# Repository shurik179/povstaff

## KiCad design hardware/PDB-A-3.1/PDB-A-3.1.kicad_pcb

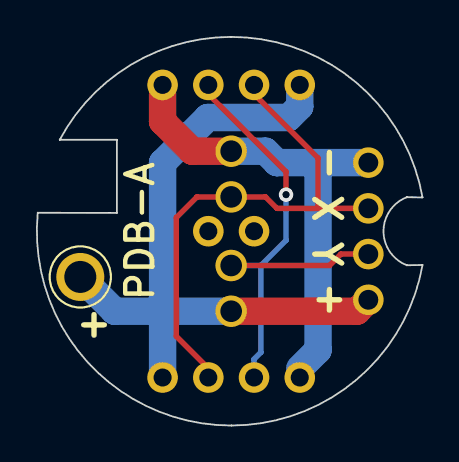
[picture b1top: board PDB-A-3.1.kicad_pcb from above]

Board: 2 copper layers, 21.4 x 21.6 mm, 8 parts (0 on the bottom side), 4 nets.

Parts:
J1: Wire solder pad; TestPoint_Plated_Hole_D2.0mm
J2, J6, J7, J8: Conn_01x01; connector-1p-generic-1.2mm-nosilk
J3: Controller conn; connector-4p-generic-nosilk
J4, J5: LED conn; connector-4p-generic-nosilk

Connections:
/GND: J2.1, J3.1, J4.4, J5.4
/VCC: J1.1, J3.4, J4.1, J5.1, J8.1
unnamed: J3.2, J4.2, J5.2, J6.1
unnamed: J3.3, J4.3, J5.3, J7.1

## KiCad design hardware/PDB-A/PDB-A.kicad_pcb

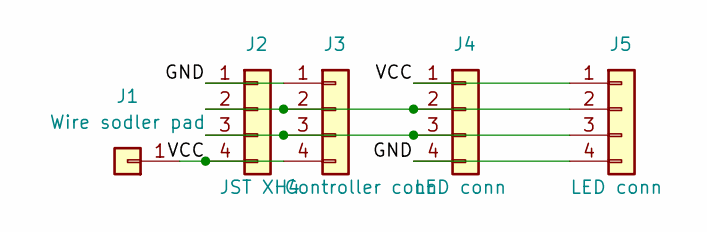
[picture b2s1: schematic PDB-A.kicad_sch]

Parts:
J1: Wire sodler pad; TestPoint_Plated_Hole_D2.0mm
J2: JST XH4; JST_XH_B4B-XH-A_1x04_P2.50mm_Vertical
J3: Controller conn; connector-4p-generic-nosilk
J4, J5: LED conn; connector-4p-generic-nosilk

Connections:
/GND: J2.1, J3.1, J4.4, J5.4
/VCC: J1.1, J2.4, J3.4, J4.1, J5.1
unnamed: J2.2, J3.2, J4.2, J5.2
unnamed: J2.3, J3.3, J4.3, J5.3

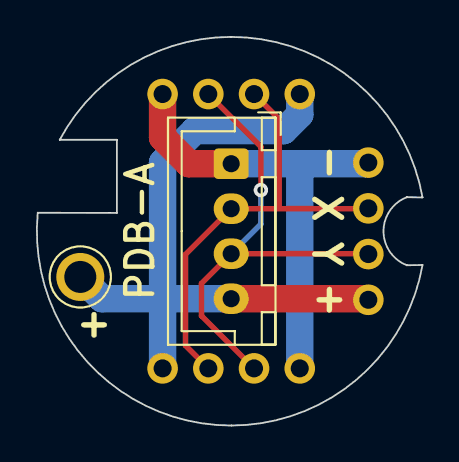
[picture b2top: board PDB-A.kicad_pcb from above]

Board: 2 copper layers, 21.4 x 21.6 mm, 5 parts (0 on the bottom side), 4 nets.

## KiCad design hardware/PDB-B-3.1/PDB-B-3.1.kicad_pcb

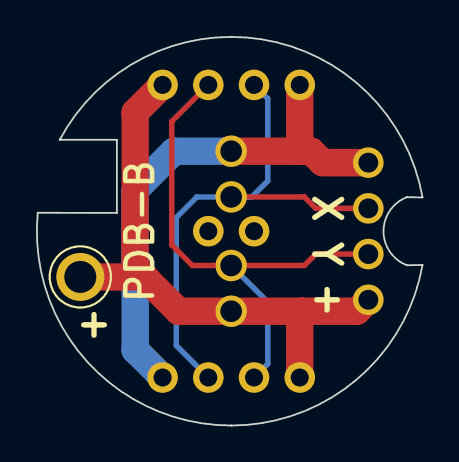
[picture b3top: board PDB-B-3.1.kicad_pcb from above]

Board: 2 copper layers, 21.4 x 21.6 mm, 8 parts (0 on the bottom side), 4 nets.

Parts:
J1, J6, J7, J8: Conn_01x01; connector-1p-generic-1.2mm-nosilk
J2, J3: LED conn; connector-4p-generic-nosilk
J4: Controller conn; connector-4p-generic-nosilk
J5: Wire solder pad; TestPoint_Plated_Hole_D2.0mm

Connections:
/GND: J1.1, J2.1, J3.1, J4.1
/VCC: J2.4, J3.4, J4.4, J5.1, J8.1
unnamed: J2.2, J3.2, J4.2, J6.1
unnamed: J2.3, J3.3, J4.3, J7.1
